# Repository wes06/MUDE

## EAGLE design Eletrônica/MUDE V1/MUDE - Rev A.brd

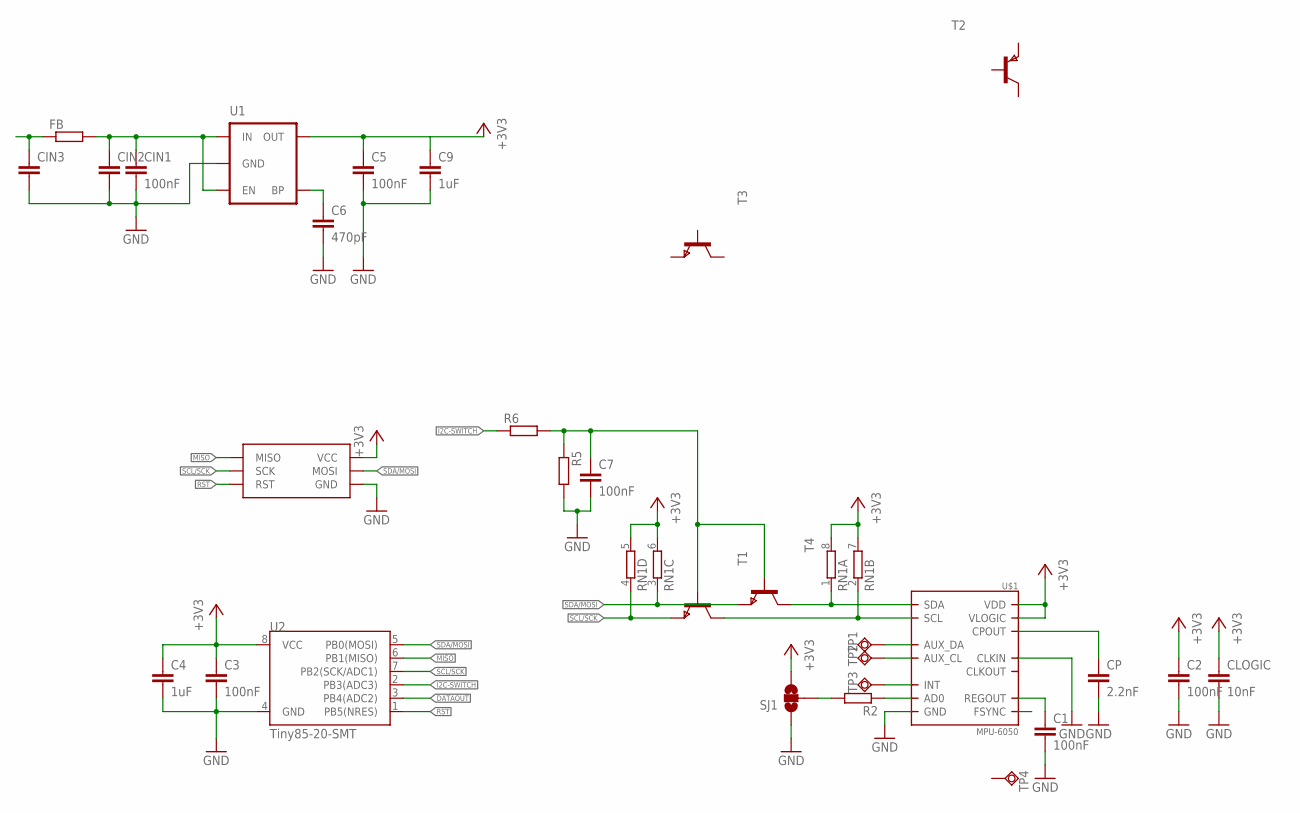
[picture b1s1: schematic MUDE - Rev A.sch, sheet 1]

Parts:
C1, C2, C3, C5, C7: 100nF; C0603
C4, C9: 1uF; C0603
C6: 470pF; C0603
CIN1: 100nF; C0603
CIN2, CIN3: C-EUC0805; C0805
CLOGIC: 10nF; C0603
CP: 2.2nF; C0603
FB: R-EU_R0603; R0603
R2, R5, R6: R-EU_R0603; R0603
RN1: 4R-N0603-ARV; 0603-ARV
SJ1: SOLDERJUMPER_2WAYS; SJ_3
T1, T3, T4: NPNSOT323; SOT323
T2: PNPSOT323; SOT323
TP1, TP2, TP3: TPSQTP10R; TP10R
TP4: TPSQTP14R; TP14R
U1: MIC52053.3V; SOT23-5
U2: Tiny85-20-SMT; SO08-EIAJ
U$1: MPU-6050; QFN.24.4X4
U$3: ISP_POGOISP_POGO; ISP_POGO

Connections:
+3V3: C2.1, C3.1, C4.1, C5.1, C9.1, CLOGIC.1, RN1.5 (2), RN1.6 (2), RN1.7 (2), RN1.8 (2), SJ1.3, U1.5 (OUT), U2.8 (VCC), U$1.8 (VLOGIC), U$1.13 (VDD), U$3.VCC
DATAOUT: U2.3 (PB4(ADC2))
GND: C1.2, C2.2, C3.2, C4.2, C5.2, C6.2, C7.2, C9.2, CIN1.2, CIN2.2, CIN3.2, CLOGIC.2, CP.2, R5.2, SJ1.1, U1.2 (GND), U2.4 (GND), U$1.1 (CLKIN), U$1.18 (GND), U$3.GND
I2C-SWITCH: R6.1, U2.2 (PB3(ADC3))
MISO: U2.6 (PB1(MISO)), U$3.MISO
unnamed: CP.1, U$1.20 (CPOUT)
unnamed: R2.1, U$1.9 (AD0)
unnamed: CIN1.1, CIN2.1, FB.2, U1.1 (IN), U1.3 (EN)
unnamed: TP1.TP, U$1.6 (AUX_DA)
unnamed: C6.1, U1.4 (BP)
unnamed: TP2.TP, U$1.7 (AUX_CL)
unnamed: RN1.1, T4.1 (C), U$1.24 (SDA)
unnamed: R2.2, SJ1.2
unnamed: RN1.2 (1), T1.1 (C), U$1.23 (SCL)
unnamed: TP3.TP, U$1.12 (INT)
unnamed: C1.1, U$1.10 (REGOUT)
unnamed: CIN3.1, FB.1
unnamed: C7.1, R5.1, R6.2, T1.2 (B), T4.2 (B)
RST: U2.1 (PB5(NRES)), U$3.RST
SCL/SCK: RN1.4 (1), T1.3 (E), U2.7 (PB2(SCK/ADC1)), U$3.SCK
SDA/MOSI: RN1.3 (1), T4.3 (E), U2.5 (PB0(MOSI)), U$3.MOSI

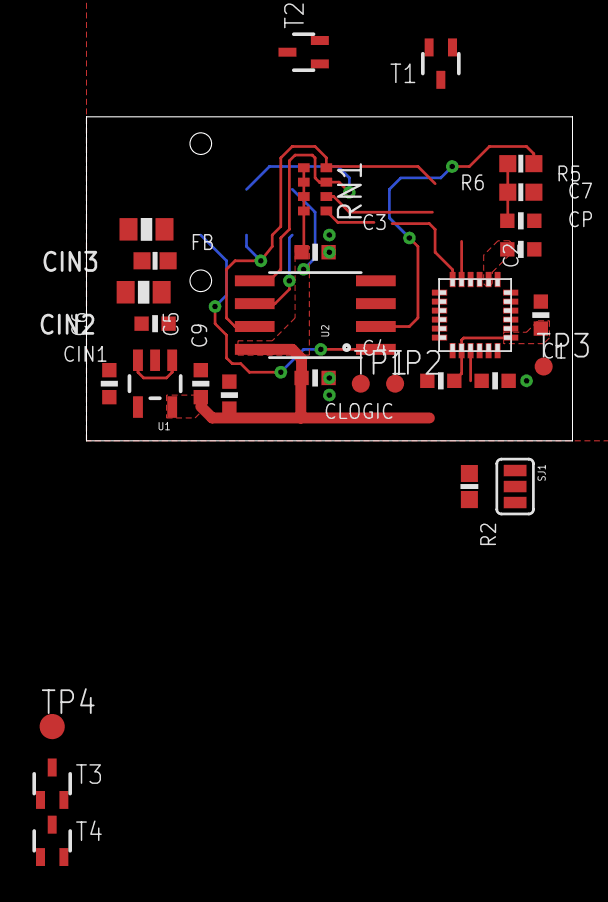
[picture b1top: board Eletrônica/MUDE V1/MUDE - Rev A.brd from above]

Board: 2 copper layers, 27.0 x 18.0 mm, 31 parts (1 on the bottom side), 20 nets.

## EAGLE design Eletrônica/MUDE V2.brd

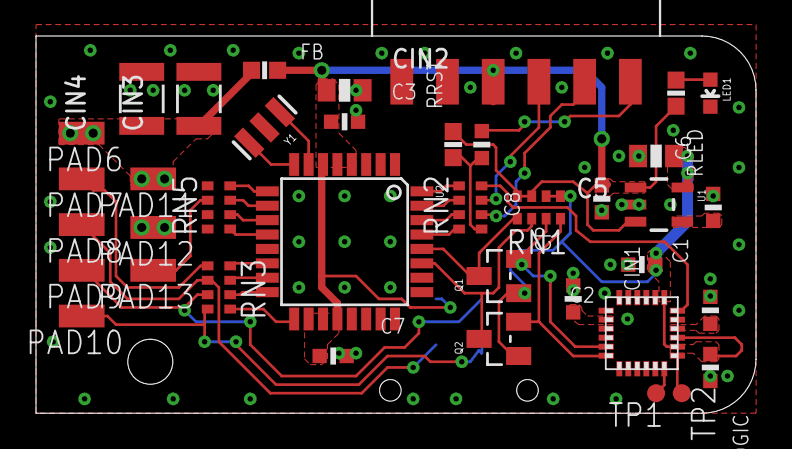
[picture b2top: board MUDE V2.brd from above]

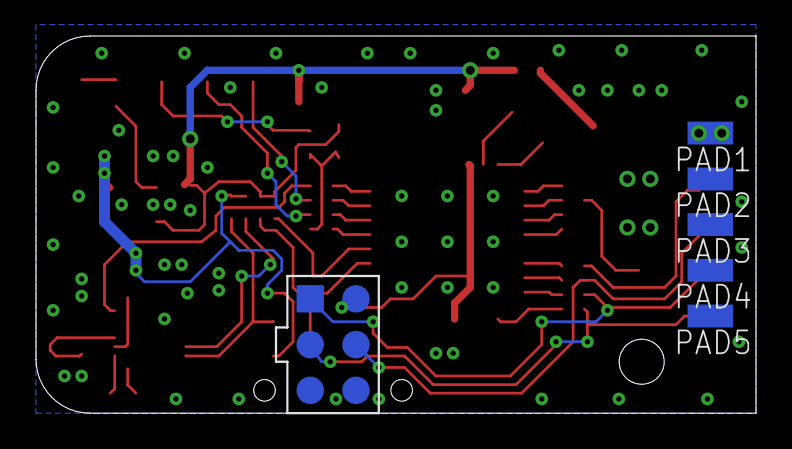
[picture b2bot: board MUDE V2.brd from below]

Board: 2 copper layers, 40.0 x 21.0 mm, 44 parts (6 on the bottom side), 38 nets.

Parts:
C1, C2, C3, C7, C8: 100nF; C0603
C5: 100nF; C0805
C6: 470pF; C0603
CIN1: 100nF; C0603
CIN2: C0805
CIN3, CIN4: C1210
CLOGIC: 10nF; C0603
CP: 2.2nF; C0603
FB: R0603
LED1: LED-0603
PAD1, PAD2, PAD3, PAD4, PAD5, PAD6, PAD7, PAD8, PAD9, PAD10, PAD11, PAD12, PAD13: SMD1,27-2,54
Q1, Q2: NFET; SOT23
RLED: R0603
RN1, RN2, RN3, RN5: 0603-ARV
RRST: R0603
TP1, TP2: TPSQTP10R; TP10R
U1: SOT23-5
U2: ATMEGA328P; TQFP32-08
U$1: MPU-6050; QFN.24.4X4
U$2: FTDI_HEADERSMD; FTDI_HEADER_SMD
U$3: ISP_POGOISP_POGO; ISP_POGO
Y1: 16MHz; RESONATOR-SMD

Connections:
+3V3: C2.1, C5.1, CLOGIC.1, Q1.1, Q2.1, RN1.5, RN1.6, U1.5, U$1.8, U$1.9, U$1.13
+5V: C3.1, C7.1, CIN1.1, CIN2.1, FB.2, RLED.2, RN1.7, RN1.8, RRST.2, U1.1, U1.3, U2.4, U2.6, U2.18, U2.20, U$2.VCC, U$3.VCC
DTR: C8.1, U$2.DTR
GND: C1.2, C2.2, C3.2, C5.2, C6.2, C7.2, CIN1.2, CIN2.2, CIN3.2, CIN4.2, CLOGIC.2, CP.2, LED1.C, PAD2.1, PAD3.1, PAD4.1, PAD5.1, PAD12.1, U1.2, U2.3, U2.5, U2.21, U$1.1, U$1.18, U$2.GND, U$3.GND, Y1.2
MISO: PAD9.1, RN3.7, U$3.MISO
MOSI: PAD8.1, RN3.6, U$3.MOSI
MPU_INT: RN2.8, U$1.12
unnamed: CP.1, U$1.20
unnamed: RN2.3, U2.30
unnamed: TP1.TP, U$1.6
unnamed: C6.1, U1.4
unnamed: TP2.TP, U$1.7
unnamed: Q2.2, RN1.4, U$1.24
unnamed: RN5.8, U2.9
unnamed: Q1.2, RN1.3, U$1.23
unnamed: U2.7, Y1.1
unnamed: LED1.A, RLED.1
unnamed: C1.1, U$1.10
unnamed: RN2.2, U2.31
unnamed: U2.8, Y1.3
unnamed: RN5.7, U2.10
unnamed: RN2.1, U2.32
unnamed: RN2.4, U2.29
unnamed: RN5.6, U2.11
unnamed: RN3.1, U2.17
unnamed: RN3.2, U2.16
unnamed: RN3.3, U2.15
unnamed: RN3.4, U2.14
unnamed: RN5.5, U2.12
unnamed: C8.2, RN2.5, RRST.1
NEOPIXELS: PAD13.1, RN5.2
RX: RN2.6, U$2.RX
SCK: PAD10.1, RN3.8, U$3.SCK
SCL: Q1.3, RN1.1, U2.28
SDA: Q2.3, RN1.2, U2.27
SS: PAD7.1, RN3.5
TX: RN2.7, U$2.TX
V+: CIN3.1, CIN4.1, FB.1, PAD1.1, PAD6.1, PAD11.1

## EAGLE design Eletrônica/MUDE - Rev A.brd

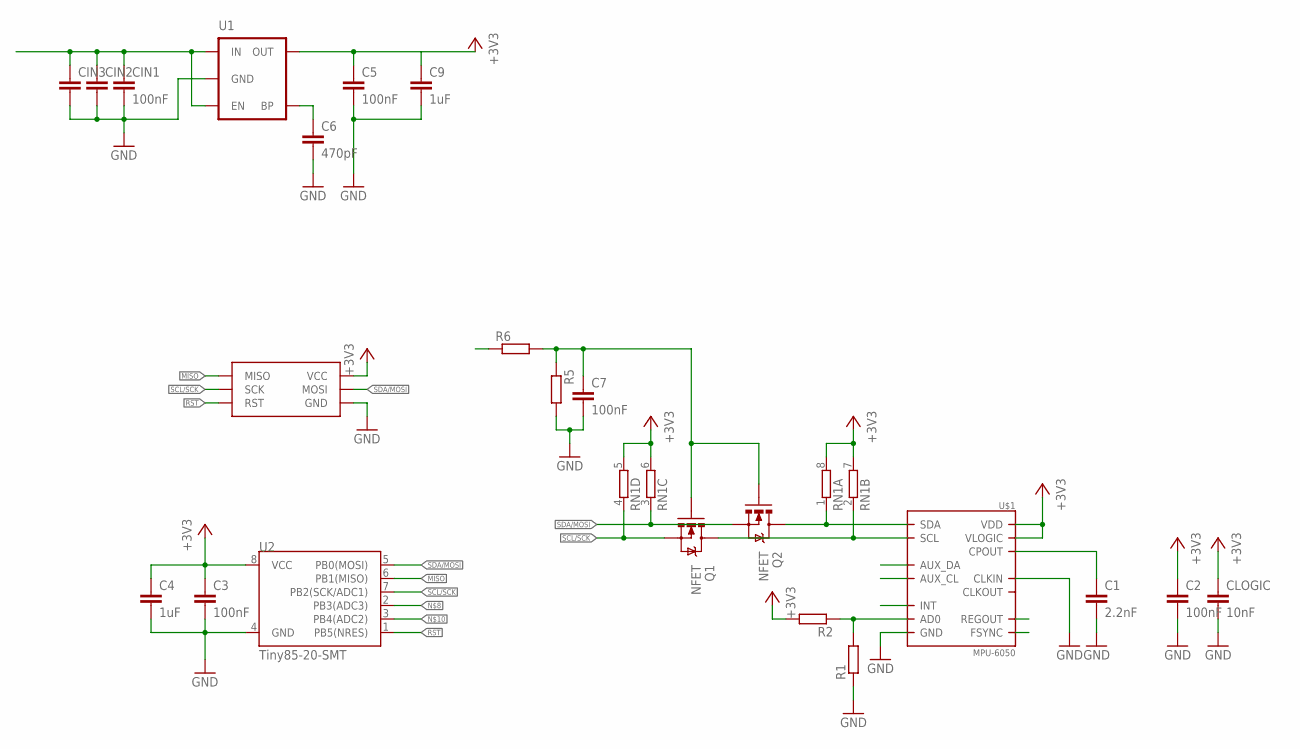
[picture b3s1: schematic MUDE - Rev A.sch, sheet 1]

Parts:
C1: 2.2nF; C0603
C2, C3, C5, C7: 100nF; C0603
C4, C9: 1uF; C0603
C6: 470pF; C0603
CIN1: 100nF; C0603
CIN2, CIN3: C-EUC0805; C0805
CLOGIC: 10nF; C0603
Q1, Q2: NFET; SOT23
R1, R2, R5, R6: R-EU_R0603; R0603
RN1: 4R-N0603-ARV; 0603-ARV
U1: MIC52053.3V; SOT23-5
U2: Tiny85-20-SMT; SO08-EIAJ
U$1: MPU-6050; QFN.24.4X4
U$3: ISP_POGOISP_POGO; ISP_POGO

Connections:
+3V3: C2.1, C3.1, C4.1, C5.1, C9.1, CLOGIC.1, R2.2, RN1.5 (2), RN1.6 (2), RN1.7 (2), RN1.8 (2), U1.5 (OUT), U2.8 (VCC), U$1.8 (VLOGIC), U$1.13 (VDD), U$3.VCC
GND: C1.2, C2.2, C3.2, C4.2, C5.2, C6.2, C7.2, C9.2, CIN1.2, CIN2.2, CIN3.2, CLOGIC.2, R1.1, R5.2, U1.2 (GND), U2.4 (GND), U$1.1 (CLKIN), U$1.18 (GND), U$3.GND
MISO: U2.6 (PB1(MISO)), U$3.MISO
unnamed: C1.1, U$1.20 (CPOUT)
unnamed: R1.2, R2.1, U$1.9 (AD0)
unnamed: CIN1.1, CIN2.1, CIN3.1, U1.1 (IN), U1.3 (EN)
unnamed: C6.1, U1.4 (BP)
unnamed: Q2.3 (D), RN1.1, U$1.24 (SDA)
unnamed: Q1.3 (D), RN1.2 (1), U$1.23 (SCL)
unnamed: C7.1, Q1.1 (G), Q2.1 (G), R5.1, R6.2
RST: U2.1 (PB5(NRES)), U$3.RST
SCL/SCK: Q1.2 (S), RN1.4 (1), U2.7 (PB2(SCK/ADC1)), U$3.SCK
SDA/MOSI: Q2.2 (S), RN1.3 (1), U2.5 (PB0(MOSI)), U$3.MOSI

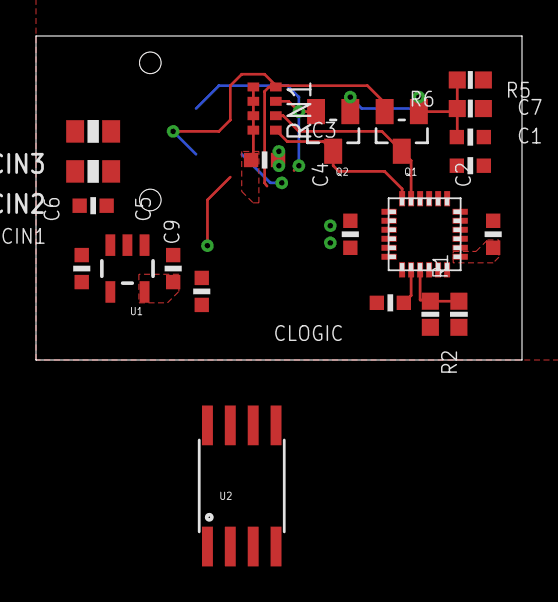
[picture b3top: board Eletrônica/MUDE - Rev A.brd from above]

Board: 2 copper layers, 27.0 x 18.0 mm, 23 parts (1 on the bottom side), 13 nets.

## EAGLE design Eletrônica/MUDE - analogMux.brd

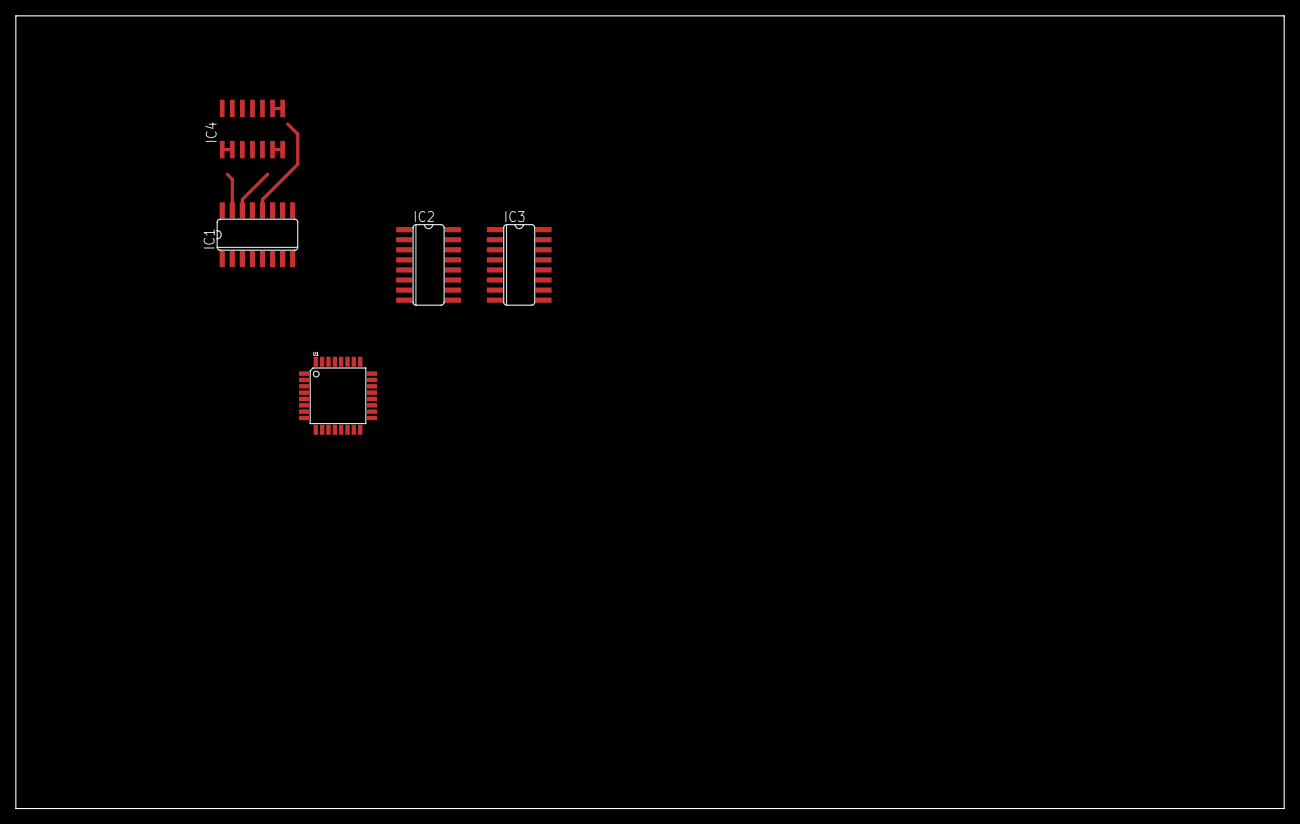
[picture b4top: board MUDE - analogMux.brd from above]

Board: 2 copper layers, 160.0 x 100.0 mm, 5 parts (0 on the bottom side), 8 nets.

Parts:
IC1, IC2, IC3: 4052D; SO16
IC4: LM324D; SO14
U1: ATMEGA168; TQFP32-08

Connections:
GND: IC1.8, IC2.8, IC3.8, IC4.11
unnamed: U1.3, U1.5, U1.21
unnamed: U1.4, U1.6
unnamed: IC1.12, IC4.8, IC4.9
unnamed: IC1.14, IC4.6, IC4.7
unnamed: IC1.15, IC4.1, IC4.2
VCC: IC1.16, IC2.16, IC3.16
VEE: IC1.7, IC2.7, IC3.7

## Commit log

2016-09-18 eagle bkp files added to .gitignore
2016-09-19 Rev A mostly finished
2016-09-19 V2 Started - atmega instead of attiny
2016-09-28 Mux draft started
2016-09-28 Test firmware for Arduino UNO created
2016-09-29 Accelerometer breakout mechanical reference
2016-09-29 MUDE V2 files
2016-09-29 Respective dirs created
2016-09-29 Gerber files for MUDE V2
2016-10-05 Added a example that uses a low pass on each accelerometer axis and if the axis value is bigger than a percentage of the low pass send the event
2016-10-06 Midi badly implemented but working for tests
2016-10-06 Draft for handmande shield
2016-10-07 Midi bug fixed by using asynchronous events
2016-10-09 Hiduino Example added for tests
2016-10-09 Accelerometer case
2016-10-10 Cable Holder created
2016-10-10 Final case designed
2016-10-10 Uno / Mega files differentiaded
2016-10-11 Removed Y axis
2016-10-11 Fotos
2016-10-12 LED animation draft corrected
2016-10-12 4 Colors per Sensor version added
2016-10-13 LED colors implemented, async corrected for LED animations
2016-10-13 Openbeam holder
2016-10-13 Final colors and calibration
2016-10-17 Recalibrated after relocation

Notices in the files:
parts and their libraries:
SparkFun-DiscreteSemi: Licensing: CC v3.0 Share-Alike You are welcome to use this library for commercial purposes.
